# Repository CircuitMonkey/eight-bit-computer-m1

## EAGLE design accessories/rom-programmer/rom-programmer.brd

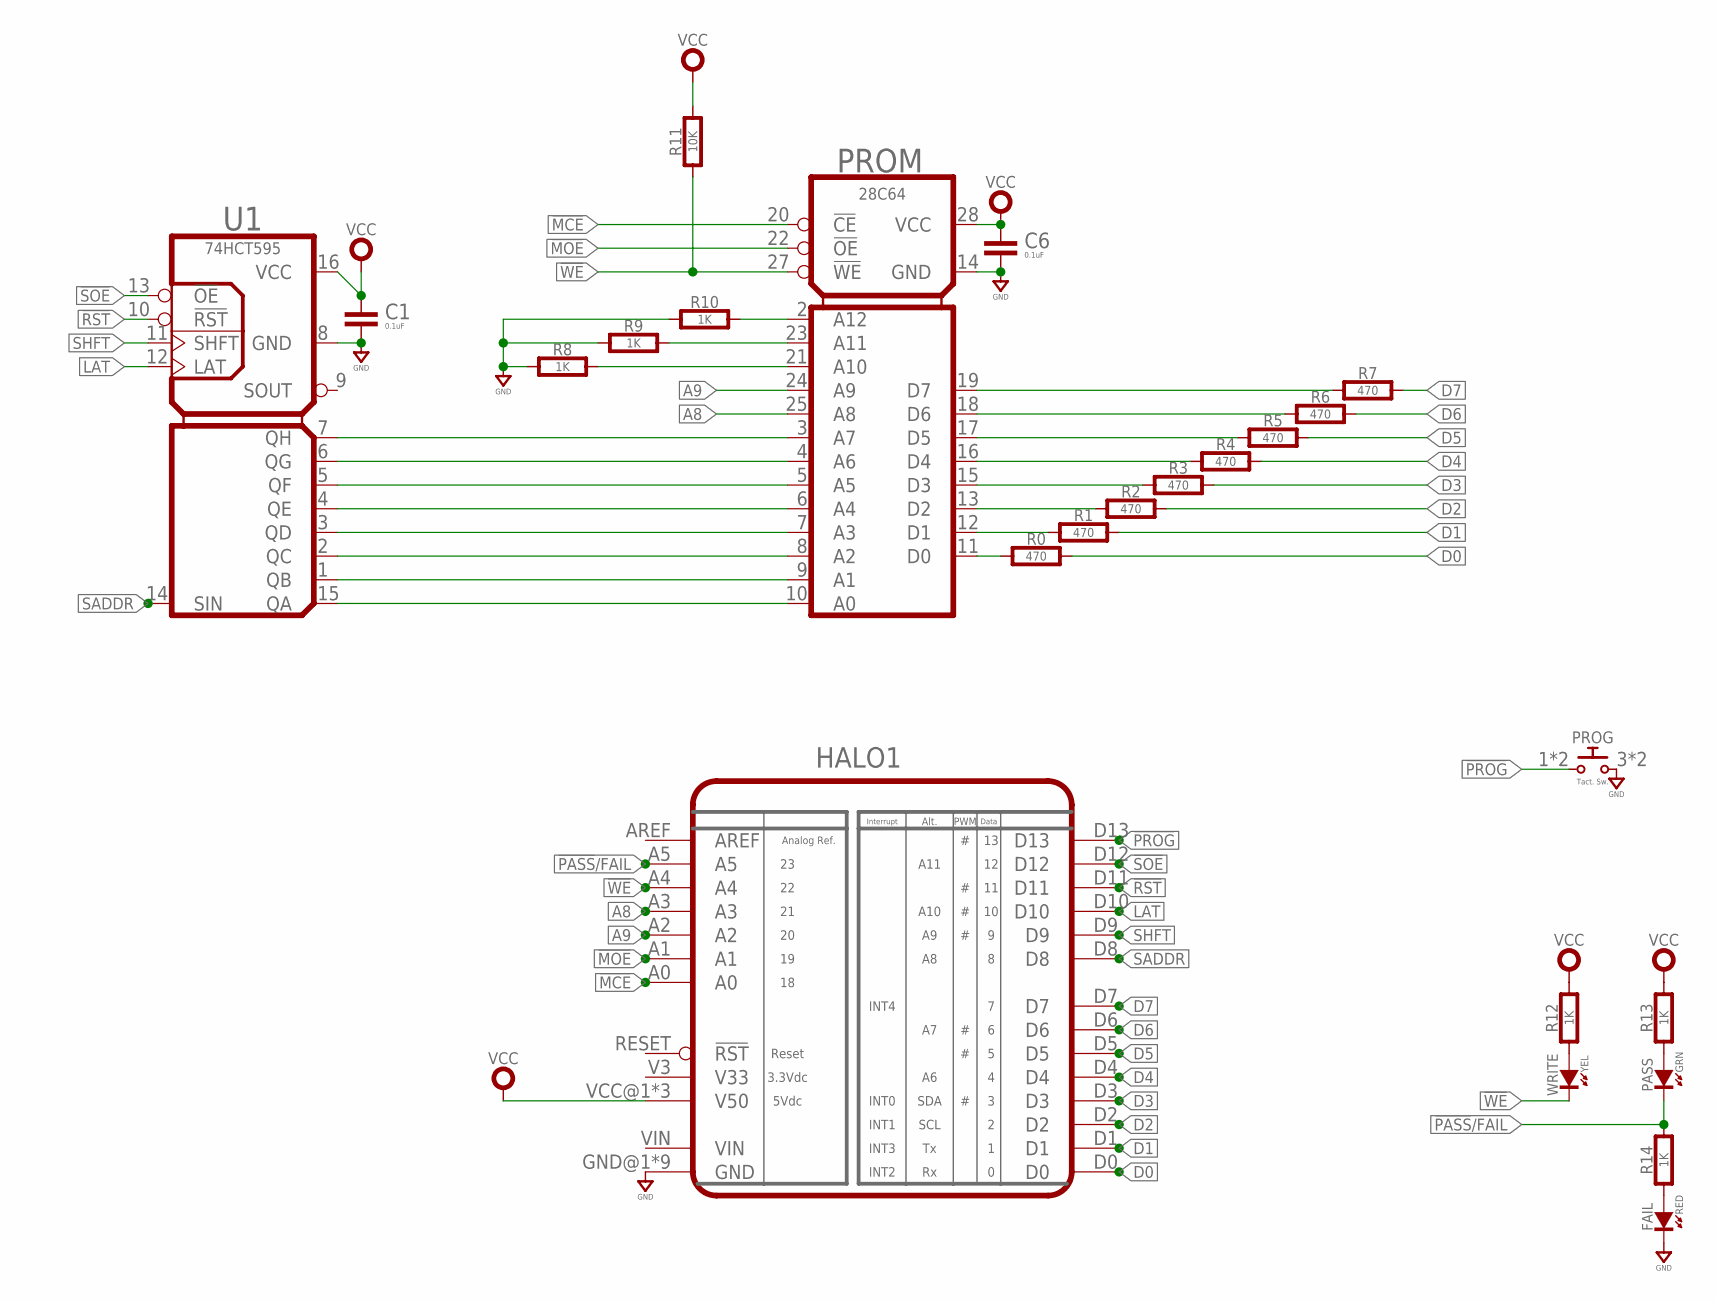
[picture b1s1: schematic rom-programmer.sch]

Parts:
C1, C6: 0.1uF; 0603-CAP
FAIL: RED; SMD_0603
HALO1: HALO-A2; PCB-HALO-A2-PINS
PASS: GRN; SMD_0603
PROG: Tact. Sw.; B3FS
PROM: 28C64; SO28
R0, R1, R2, R3, R4, R5, R6, R7: 470; 0603-RES
R8, R9, R10, R12, R13, R14: 1K; 0603-RES
R11: 10K; 0603-RES
U1: 74HCT595; SO16
WRITE: YEL; SMD_0603

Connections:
!MCE: HALO1.A0, PROM.20 (!CE)
!MOE: HALO1.A1, PROM.22 (!OE)
!PASS!/FAIL: HALO1.A5, PASS.K (C), R14.2
!PROG: HALO1.D13, PROG.1, PROG.2 (1)
!RST: HALO1.D11, U1.10 (!RST)
!SOE: HALO1.D12, U1.13 (!OE)
!WE: HALO1.A4, PROM.27 (!WE), R11.1, WRITE.K (C)
A0: PROM.10 (A0), U1.15 (QA)
A1: PROM.9 (A1), U1.1 (QB)
A2: PROM.8 (A2), U1.2 (QC)
A3: PROM.7 (A3), U1.3 (QD)
A4: PROM.6 (A4), U1.4 (QE)
A5: PROM.5 (A5), U1.5 (QF)
A6: PROM.4 (A6), U1.6 (QG)
A7: PROM.3 (A7), U1.7 (QH)
A8: HALO1.A3, PROM.25 (A8)
A9: HALO1.A2, PROM.24 (A9)
D0: HALO1.D0, R0.2
D1: HALO1.D1, R1.2
D2: HALO1.D2, R2.2
D3: HALO1.D3, R3.2
D4: HALO1.D4, R4.2
D5: HALO1.D5, R5.2
D6: HALO1.D6, R6.2
D7: HALO1.D7, R7.2
GND: C1.2, C6.2, FAIL.K (C), HALO1.GND@1 (GND), HALO1.GND@1.2 (GND), HALO1.GND@2 (GND), HALO1.GND@3 (GND), HALO1.GND@4 (GND), HALO1.MTG1 (GND), HALO1.MTG2 (GND), HALO1.MTG3 (GND), HALO1.MTG4 (GND), PROG.3 (2), PROG.4 (2), PROM.14 (GND), R8.1, R9.1, R10.1, U1.8 (GND)
LAT: HALO1.D10, U1.12 (LAT)
unnamed: FAIL.A, R14.1
unnamed: PROM.21 (A10), R8.2
unnamed: PROM.23 (A11), R9.2
unnamed: PROM.2 (A12), R10.2
unnamed: PASS.A, R13.1
unnamed: R12.1, WRITE.A
unnamed: PROM.11 (D0), R0.1
unnamed: PROM.12 (D1), R1.1
unnamed: PROM.13 (D2), R2.1
unnamed: PROM.15 (D3), R3.1
unnamed: PROM.16 (D4), R4.1
unnamed: PROM.17 (D5), R5.1
unnamed: PROM.18 (D6), R6.1
unnamed: PROM.19 (D7), R7.1
SADDR: HALO1.D8, U1.14 (SIN)
SHFT: HALO1.D9, U1.11 (SHFT)
VCC: C1.1, C6.1, HALO1.VCC@1 (V50), HALO1.VCC@2 (V50), HALO1.VCC@3 (V50), PROM.28 (VCC), R11.2, R12.2, R13.2, U1.16 (VCC)

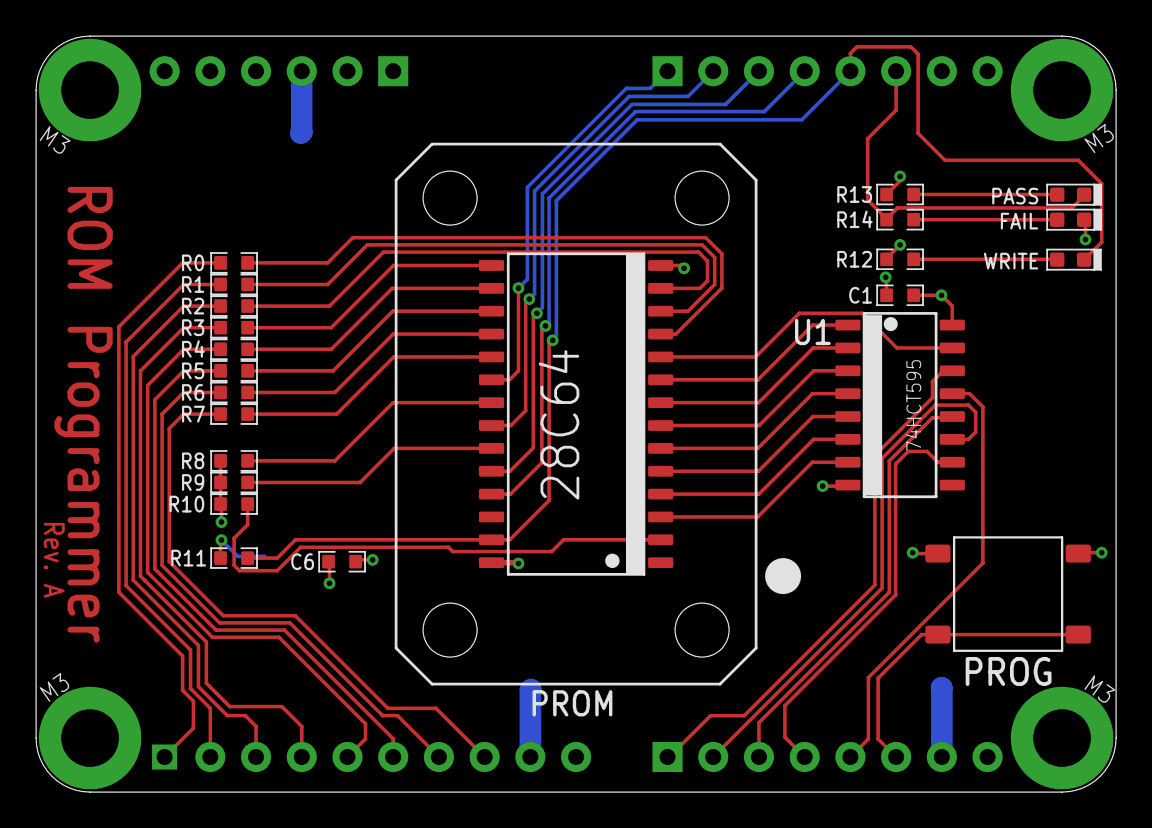
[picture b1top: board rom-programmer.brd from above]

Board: 2 copper layers, 60.0 x 42.0 mm, 24 parts (0 on the bottom side), 44 nets.

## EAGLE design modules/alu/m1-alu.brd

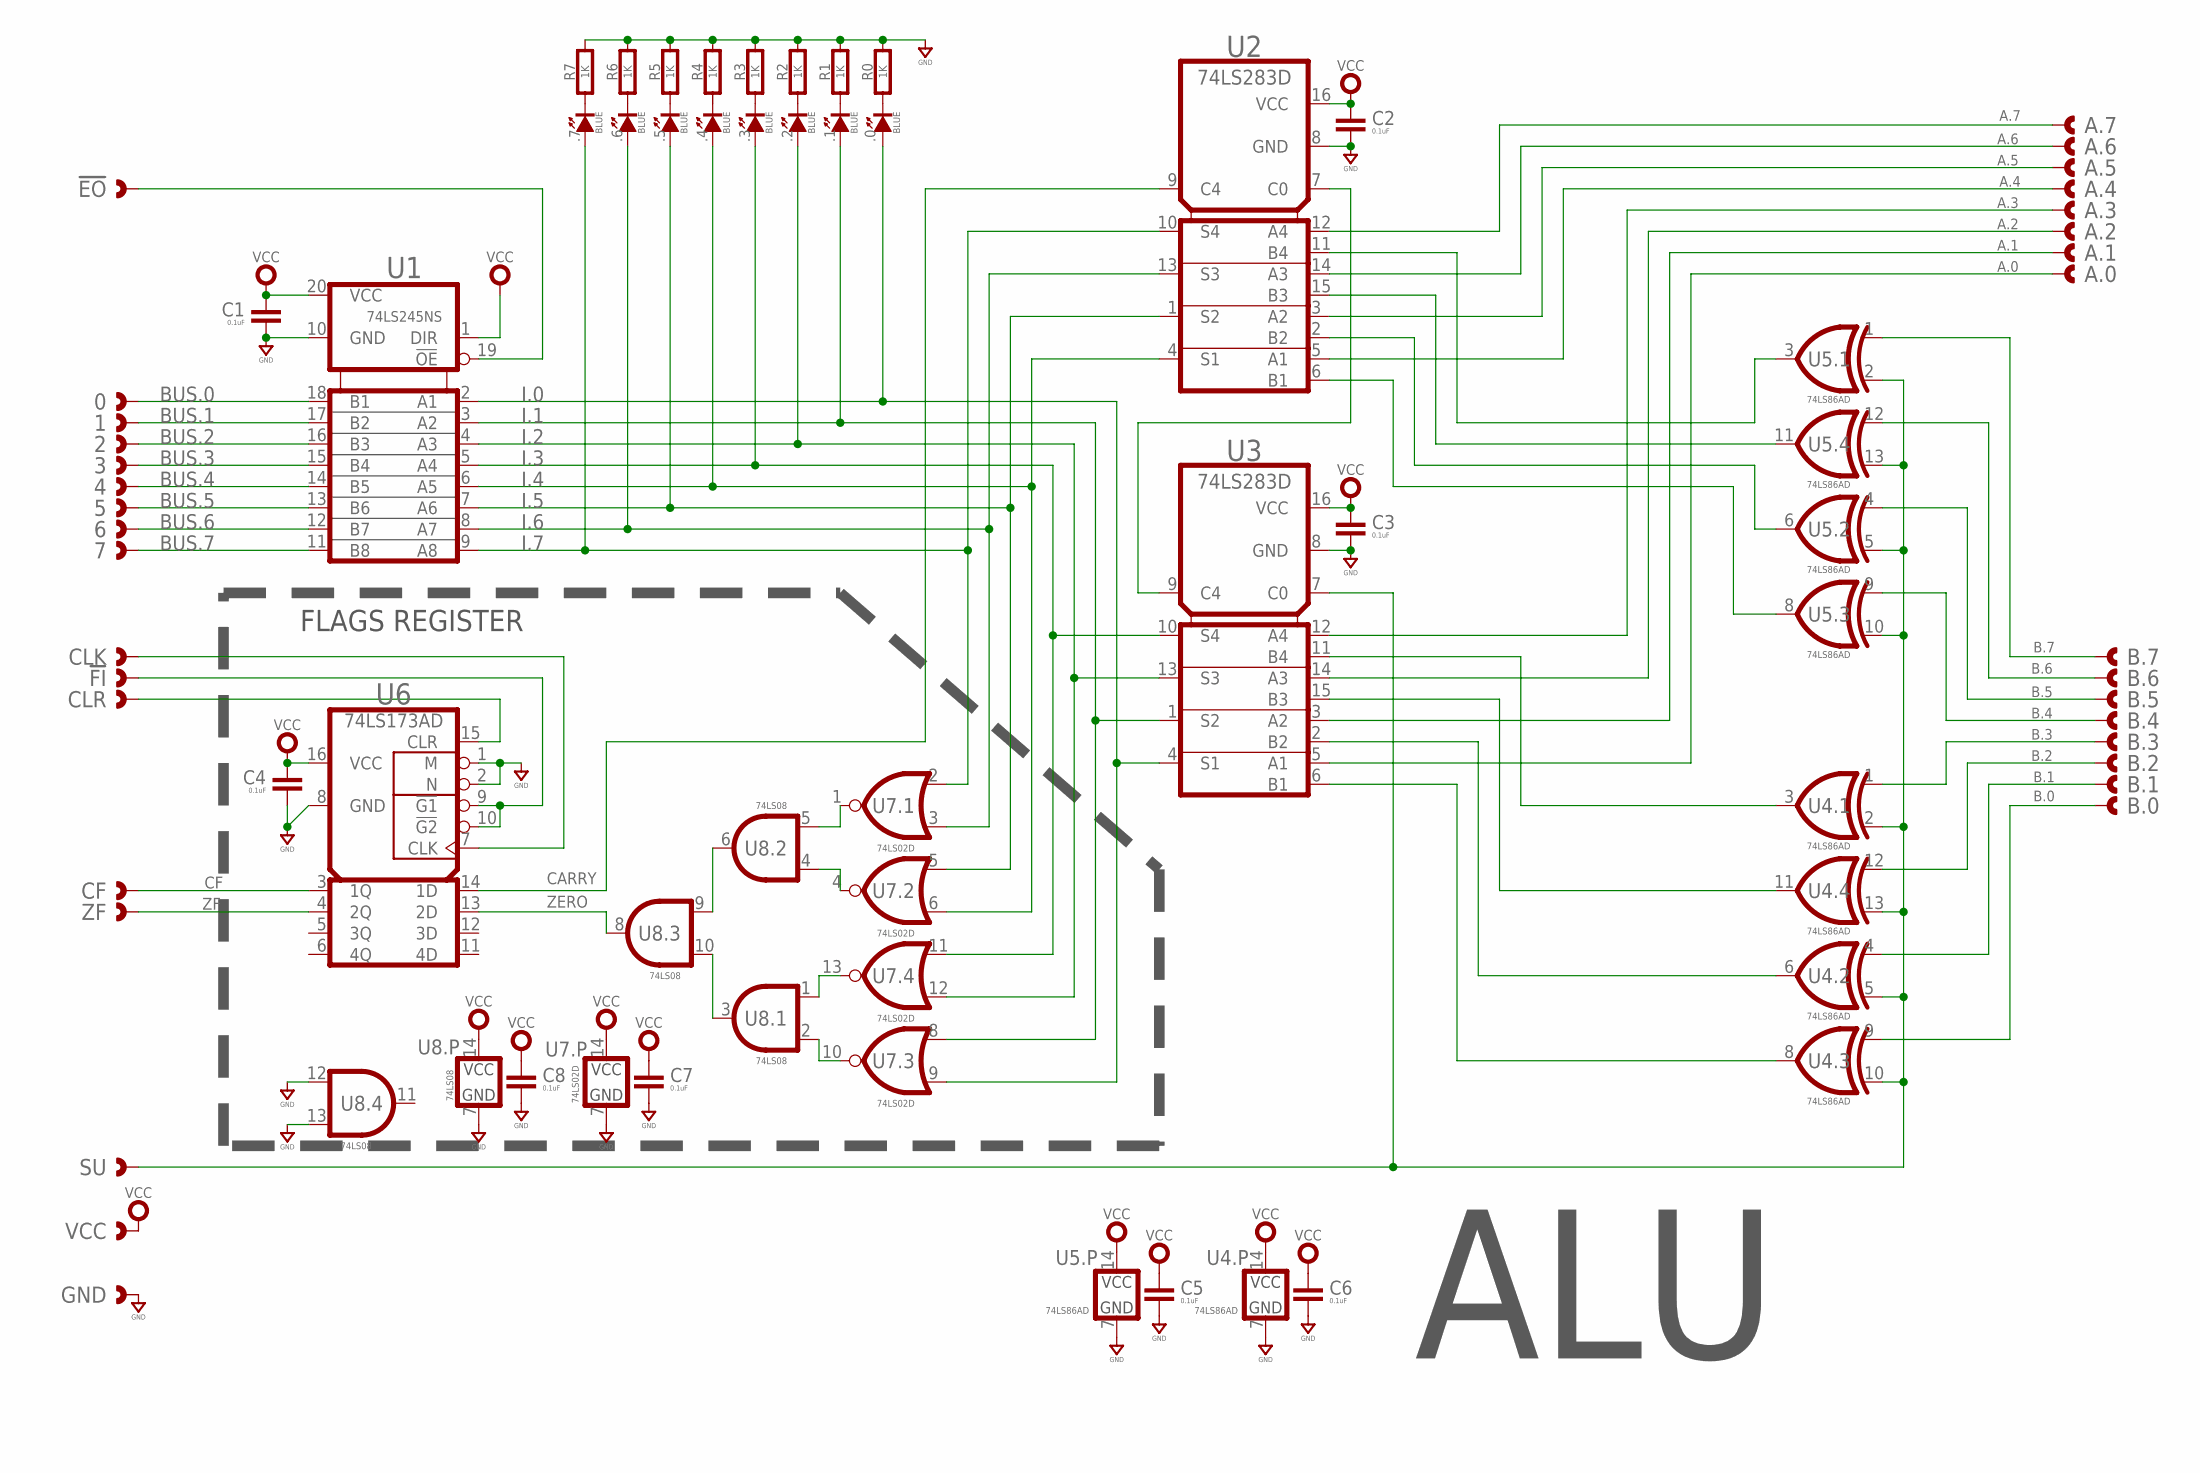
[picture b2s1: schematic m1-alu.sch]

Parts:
0, 1, 2, 3, 4, 5, 6, 7: CAST-01X1; CAST01-2.54MM
!EO: CAST-01X1; CAST01-2.54MM
!FI: CAST-01X1; CAST01-2.54MM
.0, .1, .2, .3, .4, .5, .6, .7: BLUE; SMD_0603
A.0, A.1, A.2, A.3, A.4, A.5, A.6, A.7: CAST-01X1; CAST01-2.54MM
B.0, B.1, B.2, B.3, B.4, B.5, B.6, B.7: CAST-01X1; CAST01-2.54MM
C1, C2, C3, C4, C5, C6, C7, C8: 0.1uF; 0603-CAP
CF: CAST-01X1; CAST01-2.54MM
CLK: CAST-01X1; CAST01-2.54MM
CLR: CAST-01X1; CAST01-2.54MM
GND: CAST-01X1; CAST01-2.54MM
R0, R1, R2, R3, R4, R5, R6, R7: 1K; 0603-RES
SU: CAST-01X1; CAST01-2.54MM
U1: 74LS245NS; SO20
U2, U3: 74LS283D; SO16
U4, U5: 74LS86AD; SOP14
U6: 74LS173AD; SO16
U7: 74LS02D; SOP14
U8: 74LS08; SOP14
VCC: CAST-01X1; CAST01-2.54MM
ZF: CAST-01X1; CAST01-2.54MM

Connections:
A.0: A.0.1, U3.5 (A1)
A.1: A.1.1, U3.3 (A2)
A.2: A.2.1, U3.14 (A3)
A.3: A.3.1, U3.12 (A4)
A.4: A.4.1, U2.5 (A1)
A.5: A.5.1, U2.3 (A2)
A.6: A.6.1, U2.14 (A3)
A.7: A.7.1, U2.12 (A4)
B.0: B.0.1, U4.9 (A)
B.1: B.1.1, U4.4 (A)
B.2: B.2.1, U4.12 (A)
B.3: B.3.1, U4.1 (A)
B.4: B.4.1, U5.9 (A)
B.5: B.5.1, U5.4 (A)
B.6: B.6.1, U5.12 (A)
B.7: B.7.1, U5.1 (A)
BUS.0: 0.1, U1.18 (B1)
BUS.1: 1.1, U1.17 (B2)
BUS.2: 2.1, U1.16 (B3)
BUS.3: 3.1, U1.15 (B4)
BUS.4: 4.1, U1.14 (B5)
BUS.5: 5.1, U1.13 (B6)
BUS.6: 6.1, U1.12 (B7)
BUS.7: 7.1, U1.11 (B8)
CARRY: U2.9 (C4), U6.14 (1D)
CF: CF.1, U6.3 (1Q)
GND: C1.2, C2.2, C3.2, C4.2, C5.2, C6.2, C7.2, C8.2, GND.1, R0.2, R1.2, R2.2, R3.2, R4.2, R5.2, R6.2, R7.2, U1.10 (GND), U2.8 (GND), U3.8 (GND), U4.7 (GND), U5.7 (GND), U6.1 (M), U6.2 (N), U6.8 (GND), U7.7 (GND), U8.7 (GND), U8.12 (A), U8.13 (B)
I.0: .0.A, U1.2 (A1), U3.4 (S1), U7.9 (B)
I.1: .1.A, U1.3 (A2), U3.1 (S2), U7.8 (A)
I.2: .2.A, U1.4 (A3), U3.13 (S3), U7.12 (B)
I.3: .3.A, U1.5 (A4), U3.10 (S4), U7.11 (A)
I.4: .4.A, U1.6 (A5), U2.4 (S1), U7.6 (B)
I.5: .5.A, U1.7 (A6), U2.1 (S2), U7.5 (A)
I.6: .6.A, U1.8 (A7), U2.13 (S3), U7.3 (B)
I.7: .7.A, U1.9 (A8), U2.10 (S4), U7.2 (A)
unnamed: U2.7 (C0), U3.9 (C4)
unnamed: SU.1, U3.7 (C0), U4.2 (B), U4.5 (B), U4.10 (B), U4.13 (B), U5.2 (B), U5.5 (B), U5.10 (B), U5.13 (B)
unnamed: U2.11 (B4), U5.3 (Y)
unnamed: U2.15 (B3), U5.11 (Y)
unnamed: U2.2 (B2), U5.6 (Y)
unnamed: U2.6 (B1), U5.8 (Y)
unnamed: U3.6 (B1), U4.8 (Y)
unnamed: U3.2 (B2), U4.6 (Y)
unnamed: U3.15 (B3), U4.11 (Y)
unnamed: U3.11 (B4), U4.3 (Y)
unnamed: U7.1 (Y), U8.5 (B)
unnamed: U7.4 (Y), U8.4 (A)
unnamed: U8.6 (Y), U8.9 (A)
unnamed: U8.3 (Y), U8.10 (B)
unnamed: U7.13 (Y), U8.1 (A)
unnamed: U7.10 (Y), U8.2 (B)
unnamed: !EO.1, U1.19 (!OE)
unnamed: .0.K (C), R0.1
unnamed: .1.K (C), R1.1
unnamed: .2.K (C), R2.1
unnamed: .3.K (C), R3.1
unnamed: .4.K (C), R4.1
unnamed: .5.K (C), R5.1
unnamed: .6.K (C), R6.1
unnamed: .7.K (C), R7.1
unnamed: !FI.1, U6.9 (!G1), U6.10 (!G2)
unnamed: CLK.1, U6.7 (CLK)
unnamed: CLR.1, U6.15 (CLR)
VCC: C1.1, C2.1, C3.1, C4.1, C5.1, C6.1, C7.1, C8.1, U1.20 (VCC), U2.16 (VCC), U3.16 (VCC), U4.14 (VCC), U5.14 (VCC), U6.16 (VCC), U7.14 (VCC), U8.14 (VCC), VCC.1
ZERO: U6.13 (2D), U8.8 (Y)
ZF: U6.4 (2Q), ZF.1

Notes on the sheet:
ALU
FLAGS REGISTER

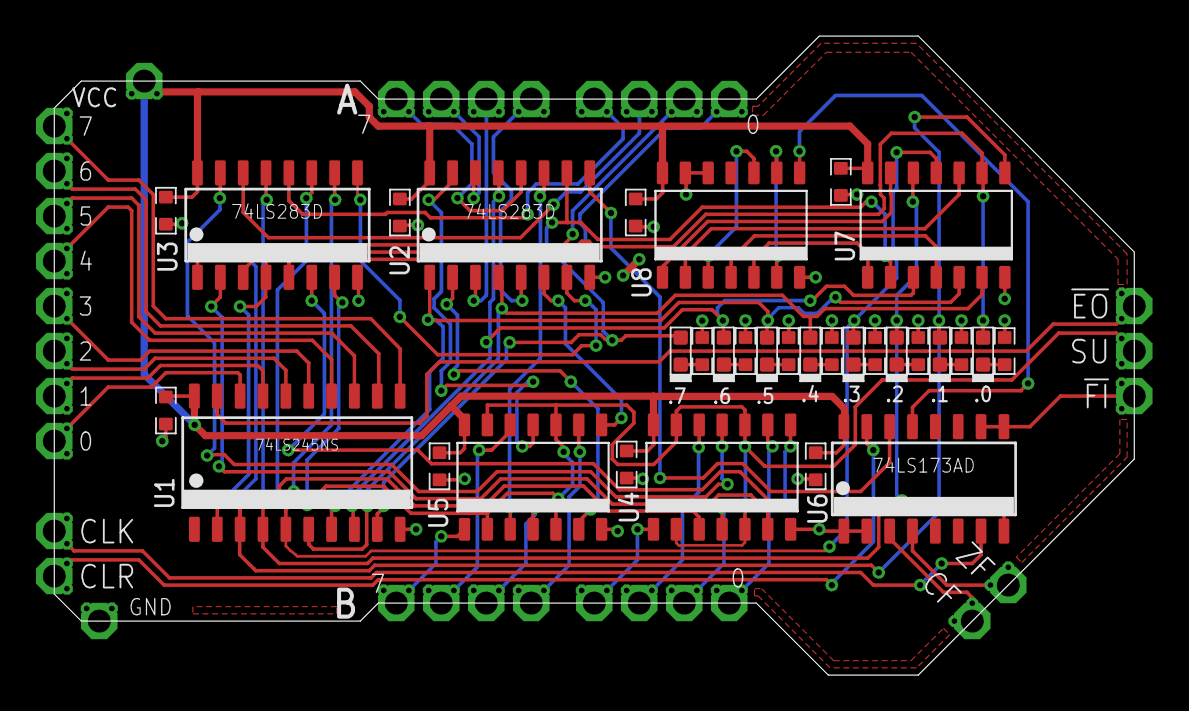
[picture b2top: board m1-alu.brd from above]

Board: 2 copper layers, 60.0 x 35.5 mm, 65 parts (0 on the bottom side), 66 nets.

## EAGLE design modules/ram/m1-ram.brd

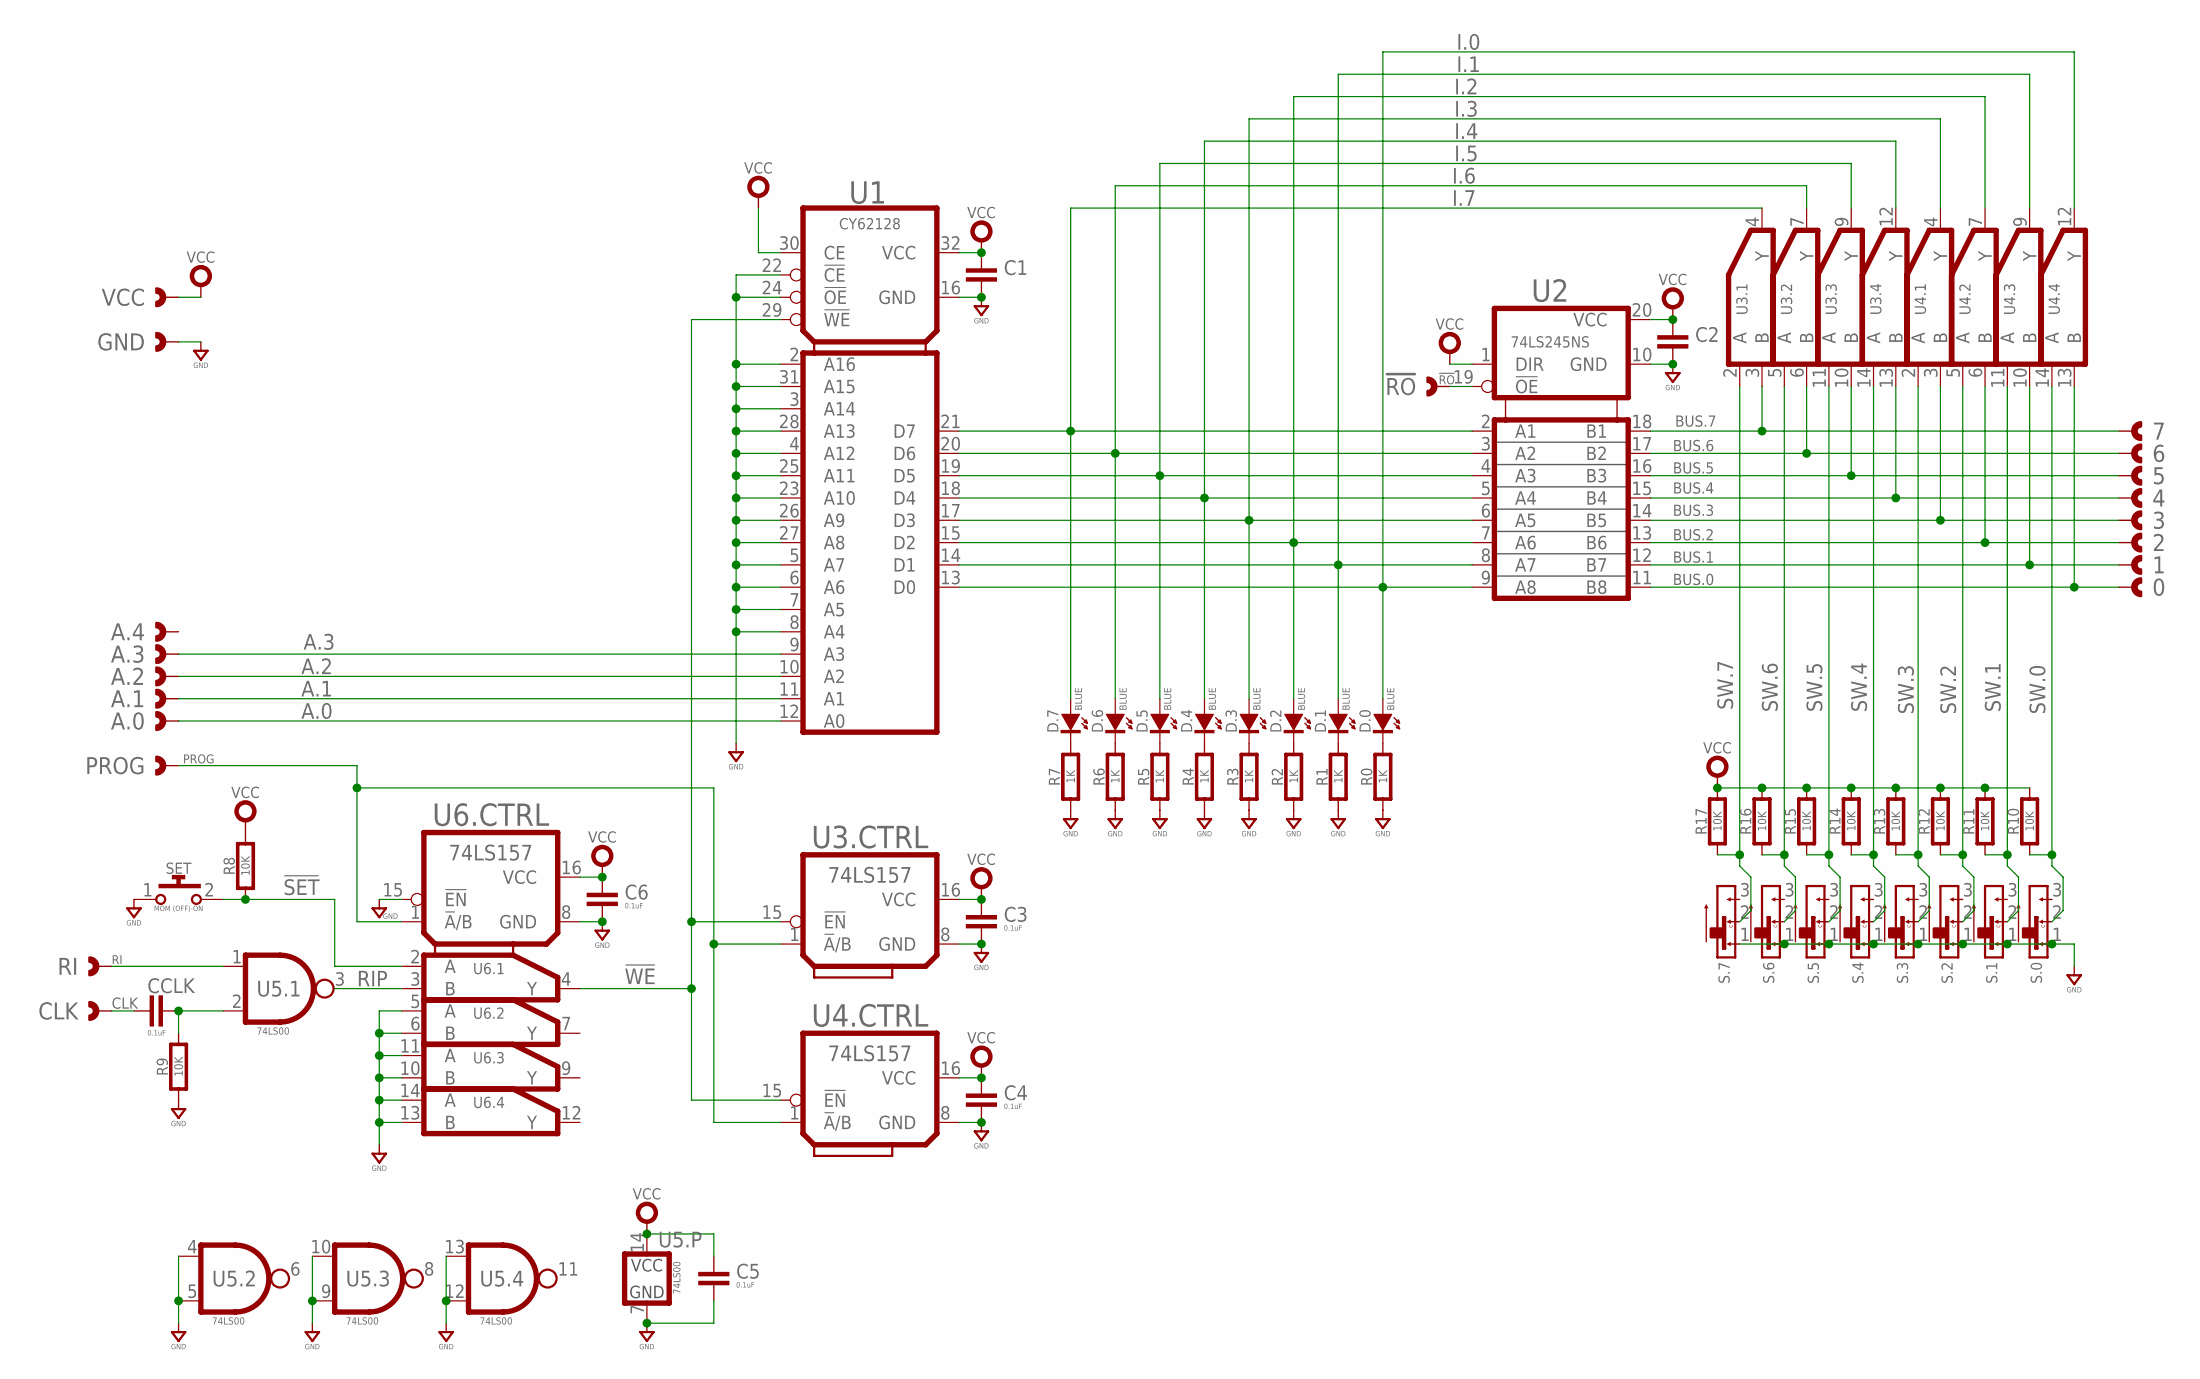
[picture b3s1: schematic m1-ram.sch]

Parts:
0, 1, 2, 3, 4, 5, 6, 7: CAST-01X1; CAST01-2.54MM
!RO: CAST-01X1; CAST01-2.54MM
A.0, A.1, A.2, A.3, A.4: CAST-01X1; CAST01-2.54MM
C1, C2: CAPACITOR0603; 0603-CAP
C3, C4, C5, C6: 0.1uF; 0603-CAP
CCLK: 0.1uF; 0603-CAP
CLK: CAST-01X1; CAST01-2.54MM
D.0, D.1, D.2, D.3, D.4, D.5, D.6, D.7: BLUE; SMD_0603
GND: CAST-01X1; CAST01-2.54MM
PROG: CAST-01X1; CAST01-2.54MM
R0, R1, R2, R3, R4, R5, R6, R7: 1K; 0603-RES
R8, R9, R10, R11, R12, R13, R14, R15, R16, R17: 10K; 0603-RES
RI: CAST-01X1; CAST01-2.54MM
S.0, S.1, S.2, S.3, S.4, S.5, S.6, S.7: SLIDE-SPDTJS102011JCQN; CK_JS102011JCQN
SET: MOM (OFF)-ON; SWITCH-0635-2P-SMD
U1: CY62128; SO32
U2: 74LS245NS; SO20
U3, U4, U6: 74LS157; SO16
U5: 74LS00; SOP14
VCC: CAST-01X1; CAST01-2.54MM

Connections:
!RO: !RO.1, U2.19 (!OE)
!SET: R8.1, SET.2, U6.2 (A)
!WE: U1.29 (!WE), U3.15 (!EN), U4.15 (!EN), U6.4 (Y)
A.0: A.0.1, U1.12 (A0)
A.1: A.1.1, U1.11 (A1)
A.2: A.2.1, U1.10 (A2)
A.3: A.3.1, U1.9 (A3)
BUS.0: 0.1, U2.11 (B8), U4.13 (B)
BUS.1: 1.1, U2.12 (B7), U4.10 (B)
BUS.2: 2.1, U2.13 (B6), U4.6 (B)
BUS.3: 3.1, U2.14 (B5), U4.3 (B)
BUS.4: 4.1, U2.15 (B4), U3.13 (B)
BUS.5: 5.1, U2.16 (B3), U3.10 (B)
BUS.6: 6.1, U2.17 (B2), U3.6 (B)
BUS.7: 7.1, U2.18 (B1), U3.3 (B)
CLK: CCLK.1, CLK.1
GND: C1.2, C2.2, C3.2, C4.2, C5.2, C6.2, GND.1, R0.1, R1.1, R2.1, R3.1, R4.1, R5.1, R6.1, R7.1, R9.1, S.0.1, S.1.1, S.2.1, S.3.1, S.4.1, S.5.1, S.6.1, S.7.1, SET.1, U1.2 (A16), U1.3 (A14), U1.4 (A12), U1.5 (A7), U1.6 (A6), U1.7 (A5), U1.8 (A4), U1.16 (GND), U1.22 (!CE), U1.23 (A10), U1.24 (!OE), U1.25 (A11), U1.26 (A9), U1.27 (A8), U1.28 (A13), U1.31 (A15), U2.10 (GND), U3.8 (GND), U4.8 (GND), U5.4 (A), U5.5 (B), U5.7 (GND), U5.9 (B), U5.10 (A), U5.12 (B), U5.13 (A), U6.5 (A), U6.6 (B), U6.8 (GND), U6.10 (B), U6.11 (A), U6.13 (B), U6.14 (A), U6.15 (!EN)
I.0: D.0.A, U1.13 (D0), U2.9 (A8), U4.12 (Y)
I.1: D.1.A, U1.14 (D1), U2.8 (A7), U4.9 (Y)
I.2: D.2.A, U1.15 (D2), U2.7 (A6), U4.7 (Y)
I.3: D.3.A, U1.17 (D3), U2.6 (A5), U4.4 (Y)
I.4: D.4.A, U1.18 (D4), U2.5 (A4), U3.12 (Y)
I.5: D.5.A, U1.19 (D5), U2.4 (A3), U3.9 (Y)
I.6: D.6.A, U1.20 (D6), U2.3 (A2), U3.7 (Y)
I.7: D.7.A, U1.21 (D7), U2.2 (A1), U3.4 (Y)
unnamed: D.0.K (C), R0.2
unnamed: CCLK.2, R9.2, U5.2 (B)
unnamed: D.1.K (C), R1.2
unnamed: D.2.K (C), R2.2
unnamed: D.3.K (C), R3.2
unnamed: D.4.K (C), R4.2
unnamed: D.5.K (C), R5.2
unnamed: D.6.K (C), R6.2
unnamed: D.7.K (C), R7.2
PROG: PROG.1, U3.1 (!A!/B), U4.1 (!A!/B), U6.1 (!A!/B)
RI: RI.1, U5.1 (A)
RIP: U5.3 (Y), U6.3 (B)
SW.0: R10.1, S.0.2, U4.14 (A)
SW.1: R11.1, S.1.2, U4.11 (A)
SW.2: R12.1, S.2.2, U4.5 (A)
SW.3: R13.1, S.3.2, U4.2 (A)
SW.4: R14.1, S.4.2, U3.14 (A)
SW.5: R15.1, S.5.2, U3.11 (A)
SW.6: R16.1, S.6.2, U3.5 (A)
SW.7: R17.1, S.7.2, U3.2 (A)
VCC: C1.1, C2.1, C3.1, C4.1, C5.1, C6.1, R8.2, R10.2, R11.2, R12.2, R13.2, R14.2, R15.2, R16.2, R17.2, U1.30 (CE), U1.32 (VCC), U2.1 (DIR), U2.20 (VCC), U3.16 (VCC), U4.16 (VCC), U5.14 (VCC), U6.16 (VCC), VCC.1

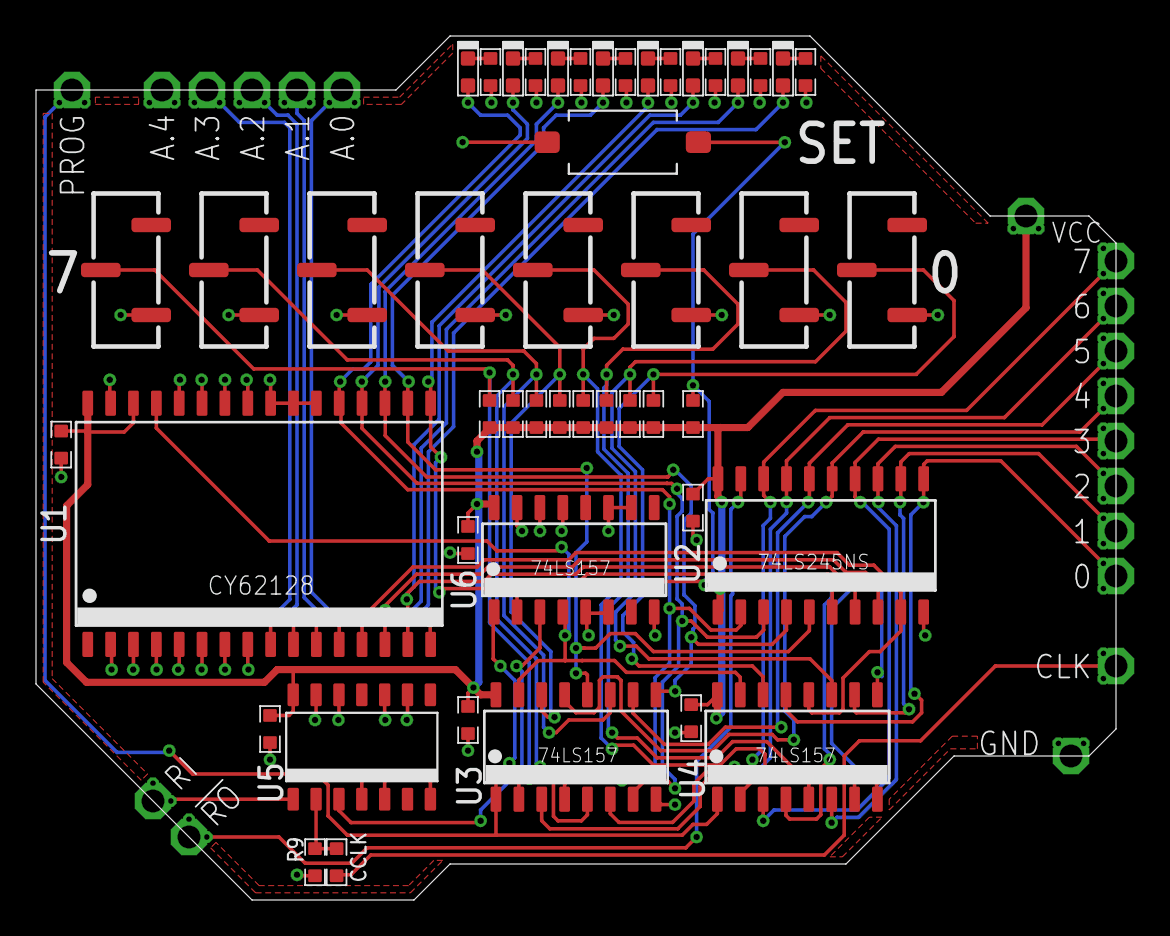
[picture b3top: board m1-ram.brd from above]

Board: 2 copper layers, 60.0 x 48.0 mm, 67 parts (0 on the bottom side), 46 nets.
